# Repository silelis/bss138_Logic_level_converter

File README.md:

# bss138_logic_level_converter
bss138 logic level converter
This is EagleCAD schematic (sch) and board (brd) files of BSS138 logic level converter.

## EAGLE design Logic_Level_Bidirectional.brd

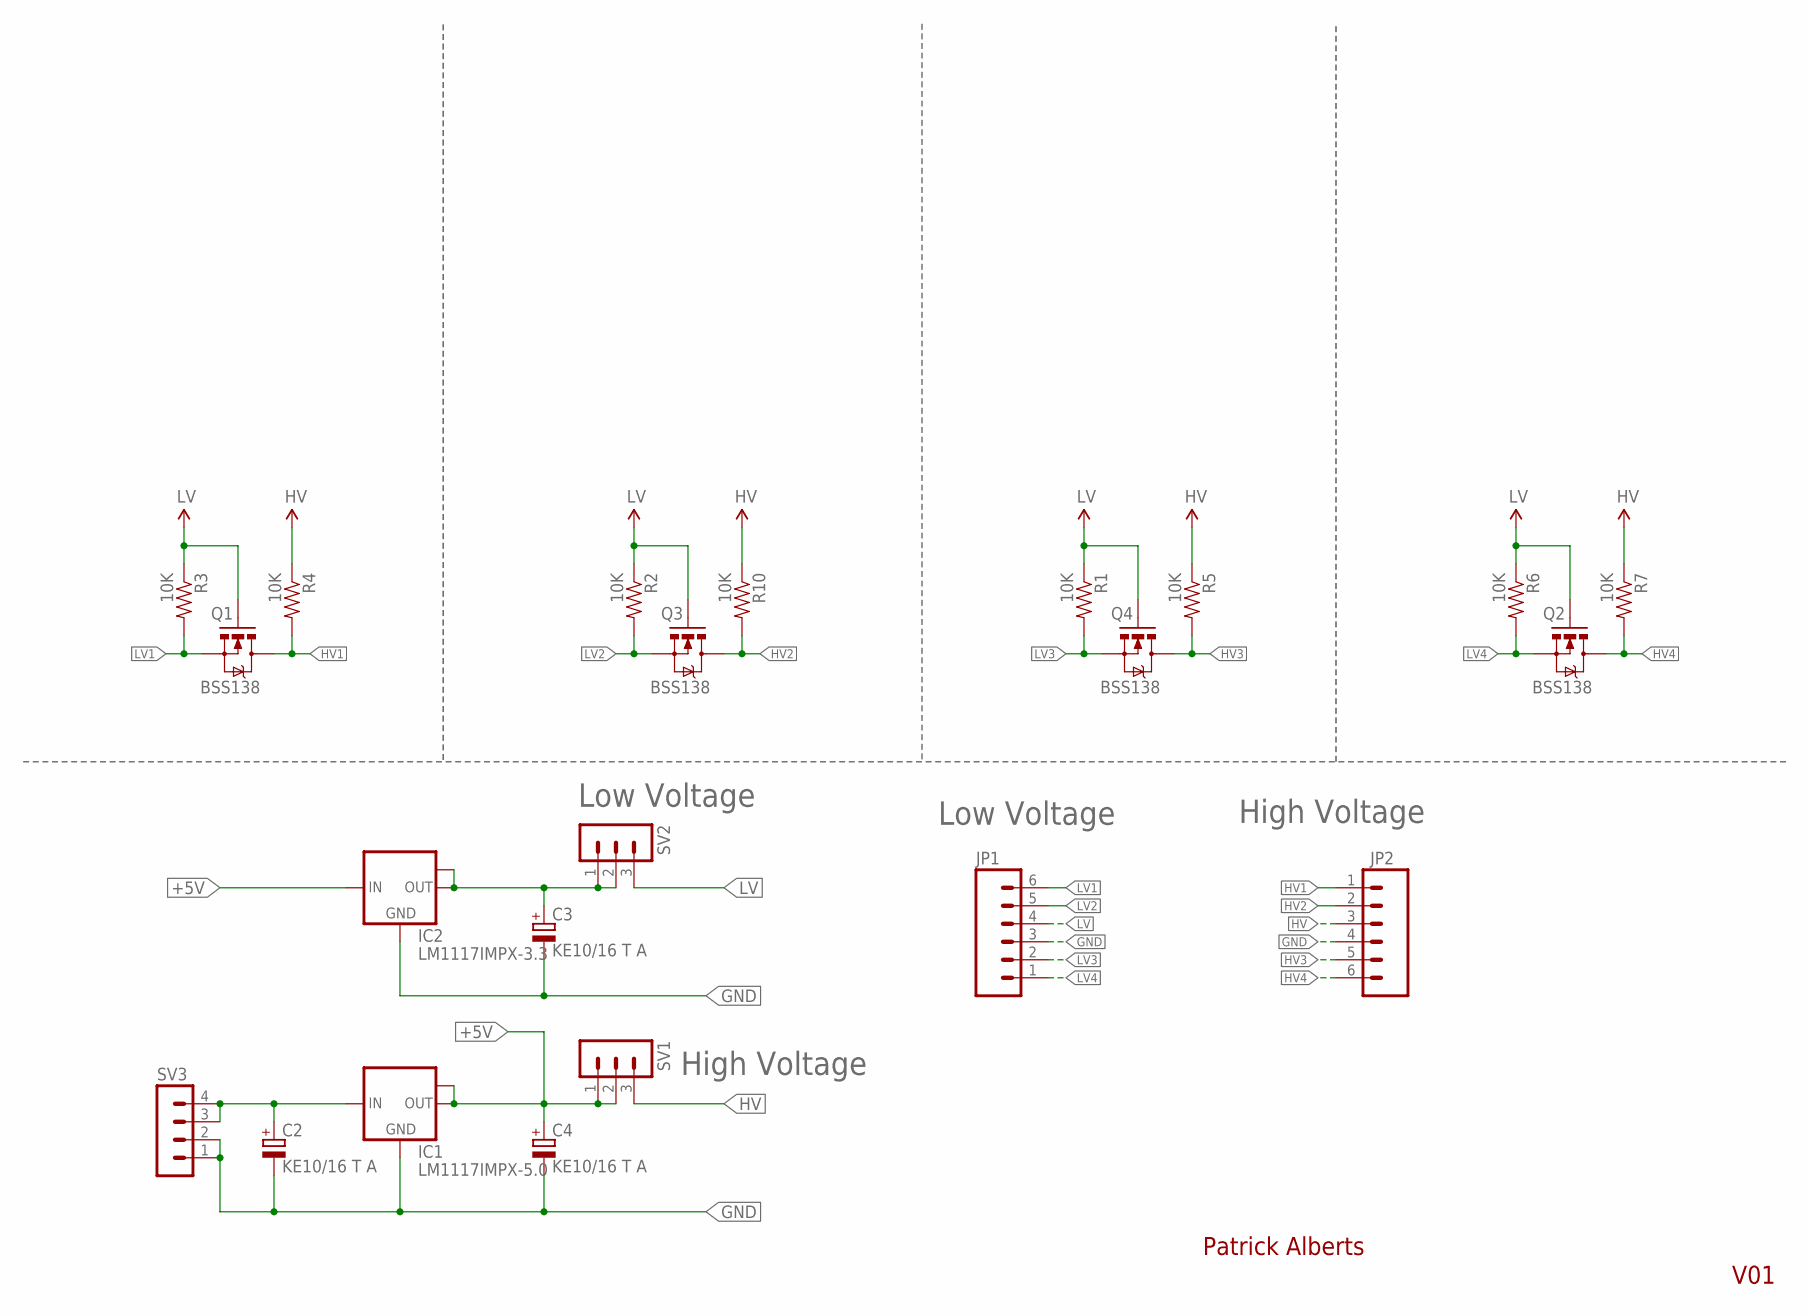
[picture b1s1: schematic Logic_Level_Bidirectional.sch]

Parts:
C2, C3, C4: KE10/16 T A; SMC_A
IC1: LM1117IMPX-5.0; SOT223
IC2: LM1117IMPX-3.3; SOT223
JP1, JP2: M06SIP; 1X06
Q1, Q2, Q3, Q4: BSS138; SOT23-3
R1, R2, R3, R4, R5, R6, R7, R10: 10K; 0603-RES
SV1, SV2: MA03-1
SV3: MA04-1

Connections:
+3.3V: C3.+, IC2.2 (OUT), IC2.TAB (OUT1), SV2.1, SV2.2
+5V: C4.+, IC1.2 (OUT), IC1.TAB (OUT1), IC2.3 (IN), SV1.1, SV1.2
GND: C2.-, C3.-, C4.-, IC1.1 (GND), IC2.1 (GND), JP1.3, JP2.4, SV3.1, SV3.2
HV: JP2.3, R4.1, R5.1, R7.1, R10.1, SV1.3
HV1: JP2.1, Q1.3 (D), R4.2
HV2: JP2.2, Q3.3 (D), R10.2
HV3: JP2.5, Q4.3 (D), R5.2
HV4: JP2.6, Q2.3 (D), R7.2
LV: JP1.4, Q1.1 (G), Q2.1 (G), Q3.1 (G), Q4.1 (G), R1.1, R2.1, R3.1, R6.1, SV2.3
LV1: JP1.6, Q1.2 (S), R3.2
LV2: JP1.5, Q3.2 (S), R2.2
LV3: JP1.2, Q4.2 (S), R1.2
LV4: JP1.1, Q2.2 (S), R6.2
unnamed: C2.+, IC1.3 (IN), SV3.3, SV3.4

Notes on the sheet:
High Voltage
Low Voltage
V01
Patrick Alberts

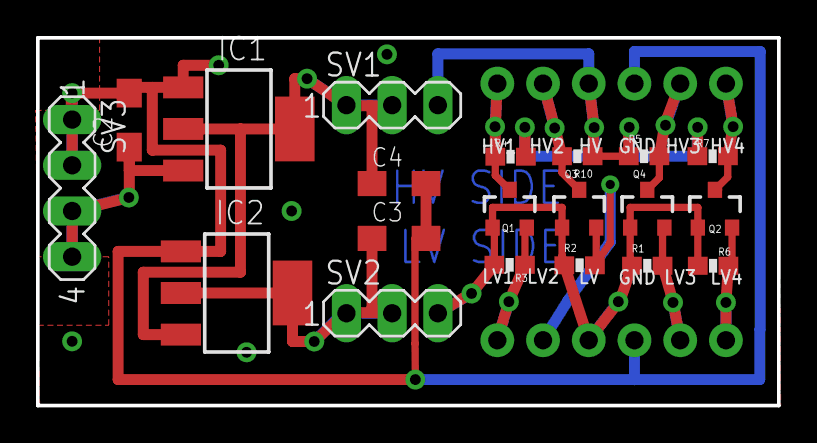
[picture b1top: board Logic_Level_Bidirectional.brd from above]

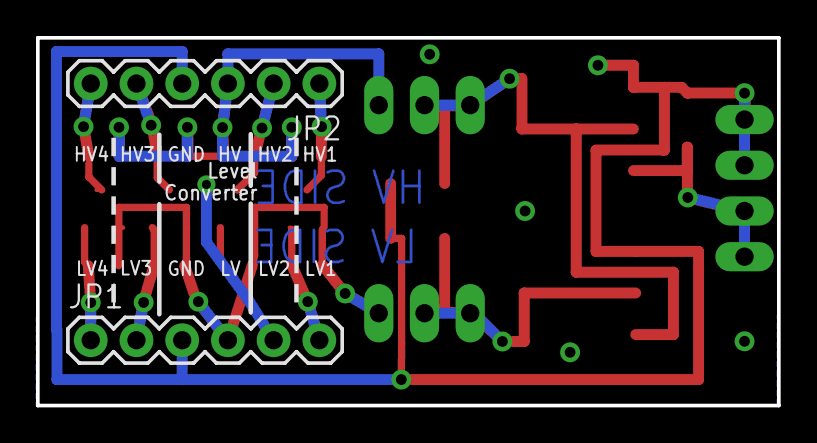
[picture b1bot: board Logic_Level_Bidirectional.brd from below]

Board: 2 copper layers, 41.2 x 20.4 mm, 22 parts (2 on the bottom side), 14 nets.

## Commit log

2023-03-22 GitTest
2023-03-22 git test

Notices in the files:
parts and their libraries:
SparkFun-Aesthetics: Licensing: CC v3.0 Share-Alike You are welcome to use this library for commercial purposes.
SparkFun-Aesthetics: Released under the Creative Commons
SparkFun-Aesthetics: http://creativecommons.org/licenses/by-sa/3.0
